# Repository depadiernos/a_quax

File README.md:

# a_quax

inspired by the A Dux and minidox.

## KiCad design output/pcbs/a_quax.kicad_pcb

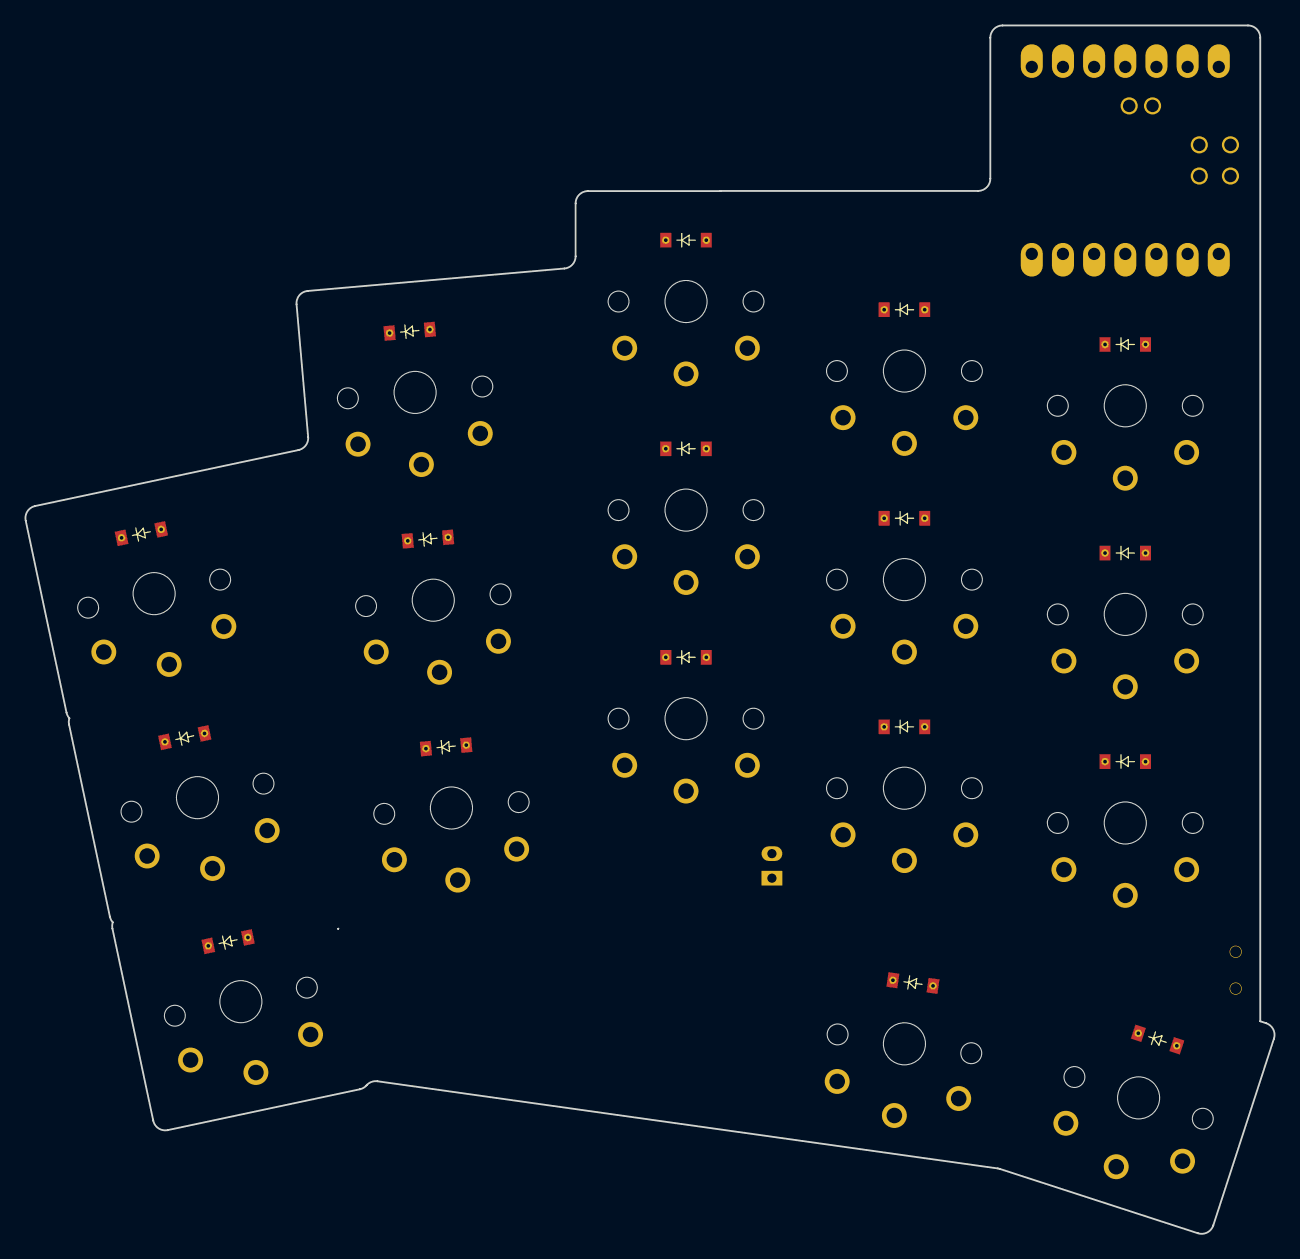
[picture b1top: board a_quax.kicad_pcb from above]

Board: 2 copper layers, 101.8 x 98.5 mm, 37 parts (0 on the bottom side), 29 nets, no tracks yet.

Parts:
D1, D2, D3, D4, D5, D6, D7, D8, D9, D10, D11, D12, D13, D14, D15, D16, D17: diode
JST1: JST_PH_S2B-PH-K_02x2.00mm_Angled
MCU1: xiao-ble
S1, S2, S3, S4, S5, S6, S7, S8, S9, S10, S11, S12, S13, S14, S15, S16, S17: PG1350
T1: SPDT_C128955

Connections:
GND: JST1.2, MCU1.2, MCU1.9, MCU1.22
P2: MCU1.16, S1.2, S2.2, S3.2
P3: MCU1.15, S4.2, S5.2, S6.2
P4: MCU1.14, S7.2, S8.2, S9.2
P5: MCU1.13, S10.2, S11.2, S12.2, S16.2
P6: MCU1.12, S13.2, S14.2, S15.2, S17.2
P7: D1.1, D4.1, D7.1, D10.1, D13.1, MCU1.7
P8: D2.1, D5.1, D8.1, D11.1, D14.1, MCU1.6
P9: D3.1, D6.1, D9.1, D12.1, D15.1, MCU1.5
P10: D16.1, D17.1, MCU1.4
RAW: MCU1.21, T1.1
RAWER: JST1.1, T1.2
first_only: D16.2, S16.1
index_bottom: D10.2, S10.1
index_home: D11.2, S11.1
index_top: D12.2, S12.1
inner_bottom: D13.2, S13.1
inner_home: D14.2, S14.1
inner_top: D15.2, S15.1
middle_bottom: D7.2, S7.1
middle_home: D8.2, S8.1
middle_top: D9.2, S9.1
pinky_bottom: D1.2, S1.1
pinky_home: D2.2, S2.1
pinky_top: D3.2, S3.1
ring_bottom: D4.2, S4.1
ring_home: D5.2, S5.1
ring_top: D6.2, S6.1
second_only: D17.2, S17.1

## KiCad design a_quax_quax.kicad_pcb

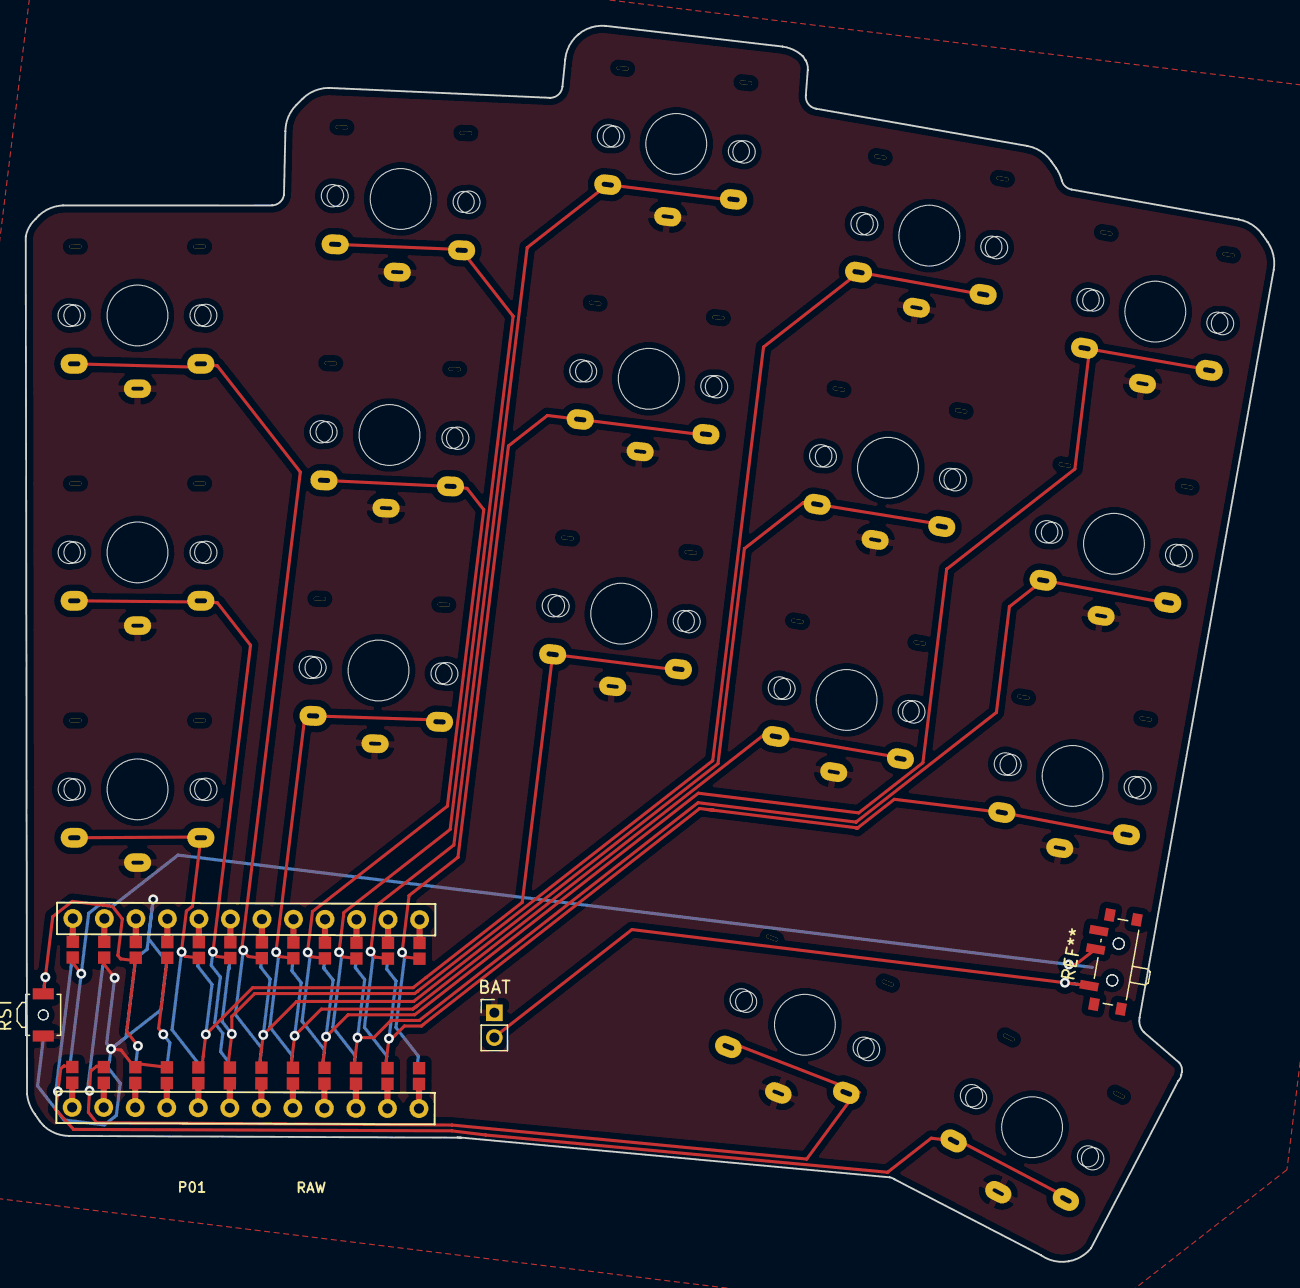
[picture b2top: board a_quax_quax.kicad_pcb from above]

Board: 2 copper layers, 100.6 x 99.6 mm, 21 parts (1 on the bottom side), 19 nets.

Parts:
BAT: PinHeader_1x02_P2.00mm_Vertical
C1: ProMicro_Jumper
RST: SW_SPST_B3U-3000P-B
RST#2: SW_SPST_B3U-3000P-B
S2, S4, S6, S8, S10, S12, S14, S16, S18, S20, S22, S24, S26, S28, S30, S32, S34: ChocV2_1u_flippable

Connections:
GND: BAT.1, C1.2, C1.21, C1.22, RST.2, RST#2.1, S2.2, S4.2, S6.2, S8.2, S10.2, S12.2, S14.2, S16.2, S18.2, S20.2, S22.2, S24.2, S26.2, S28.2, S30.2, S32.2, S34.2
P0: C1.23, S32.1
P1: C1.24, S34.1
P2: C1.20, S14.1
P3: C1.19, S24.1
P4: C1.18, S22.1
P5: C1.17, S20.1
P6: C1.16, S30.1
P7: C1.15, S28.1
P8: C1.14, S26.1
P10: C1.12, S16.1
P14: C1.10, S12.1
P15: C1.9, S10.1
P16: C1.11, S18.1
P18: C1.8, S8.1
P19: C1.7, S6.1
P20: C1.6, S4.1
P21: C1.5, S2.1
RST: C1.3, RST.1, RST#2.2

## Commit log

2021-11-21 a_quax_quax
2021-11-21 update spacing and outline
2021-11-21 update ground plane
2021-12-02 fix solder mask on choc footprint
2021-12-06 fix missing via for the power switch
2022-03-28 new iteration using ergogen
2022-03-28 add .gitignore
2022-03-28 remove old version
2022-03-28 restructure code
2022-03-28 experimental mcu placement
2022-03-29 add pcb backup
2022-03-29 moving mcu around to find the best place for it.
2022-03-30 update promicro footprint
2022-03-31 add autosave file to gitignore
